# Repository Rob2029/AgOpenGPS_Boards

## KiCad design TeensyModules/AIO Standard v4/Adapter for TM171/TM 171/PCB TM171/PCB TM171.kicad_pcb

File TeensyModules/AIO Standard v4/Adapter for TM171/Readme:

This is an adapter to use the TM171 IMU sensor using the connectors for the F9P module form ardusimple

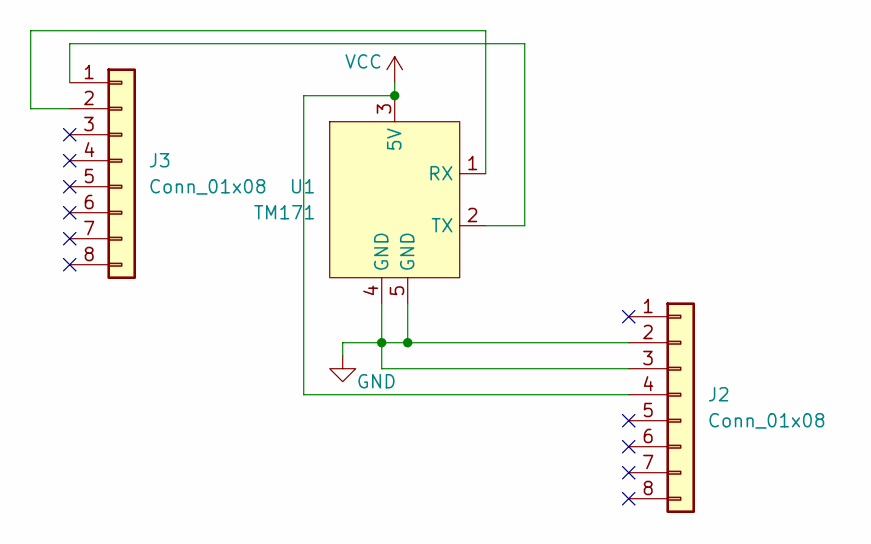
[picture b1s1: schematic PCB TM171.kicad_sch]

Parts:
J2, J3: Conn_01x08; PinHeader_1x08_P2.54mm_Vertical
U1: TM171; Untitled

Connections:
GND: J2.2, J2.3, U1.4 (GND), U1.5 (GND)
unnamed: J3.1, U1.2 (TX)
unnamed: J3.2, U1.1 (RX)
VCC: J2.4, U1.3 (5V)

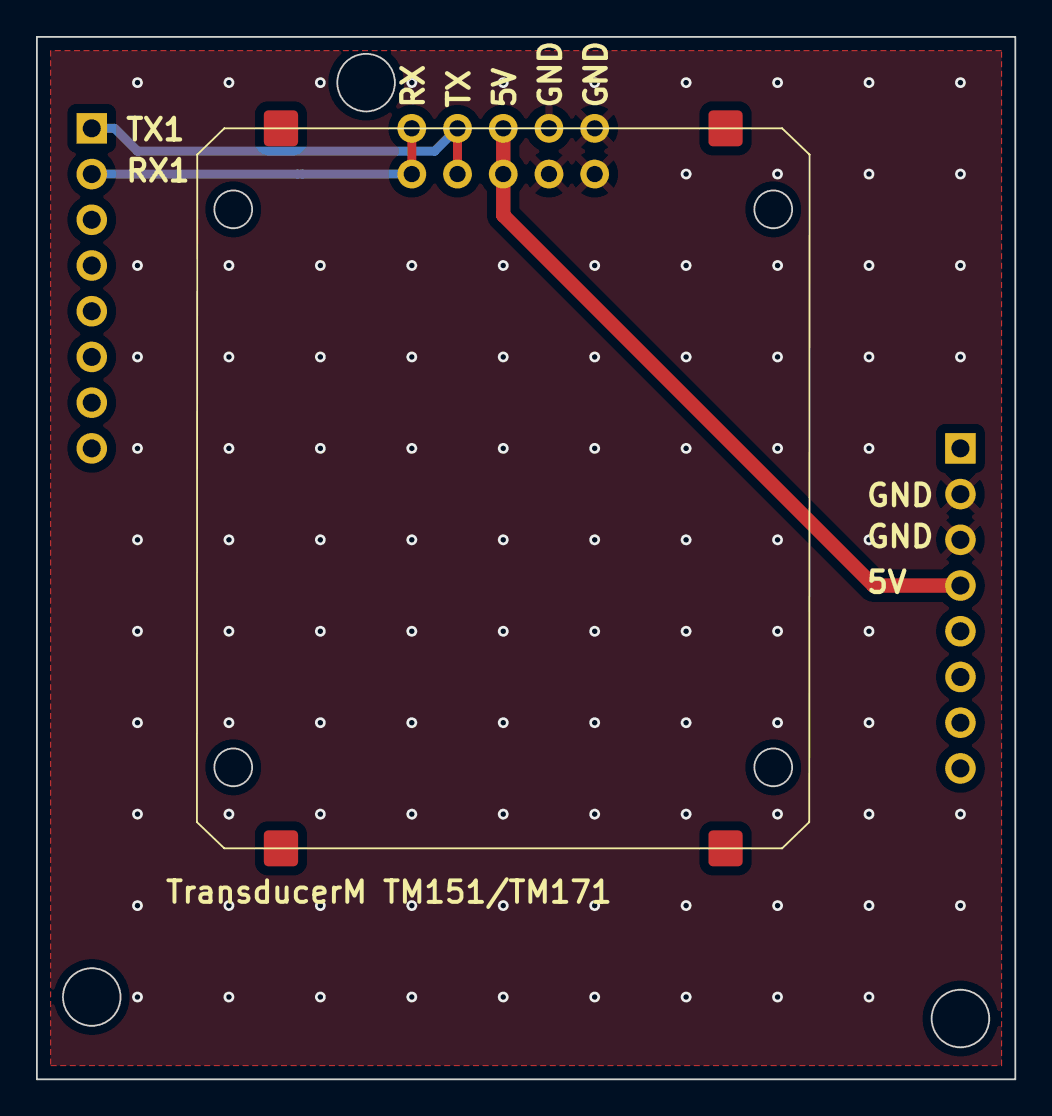
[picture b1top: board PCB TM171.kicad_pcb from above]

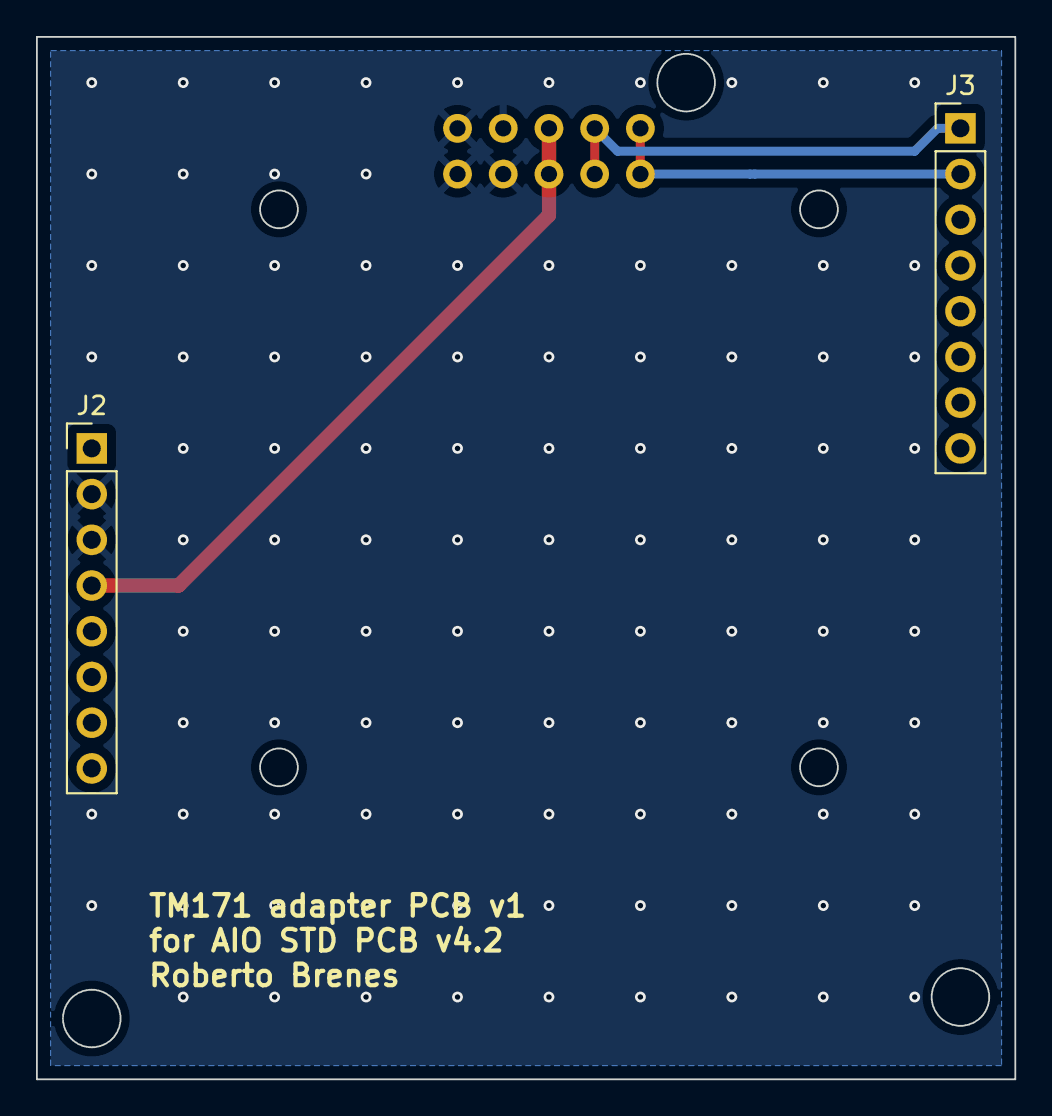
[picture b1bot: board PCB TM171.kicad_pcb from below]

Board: 2 copper layers, 54.4 x 57.9 mm, 3 parts (2 on the bottom side), 4 nets.

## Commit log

2026-01-13 Readme File
2026-01-31 Files for kicad and manfacturing
